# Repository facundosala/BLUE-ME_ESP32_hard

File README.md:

# BLUE-ME_ESP32_hardware
Hardware esp32 for use Blue And Me

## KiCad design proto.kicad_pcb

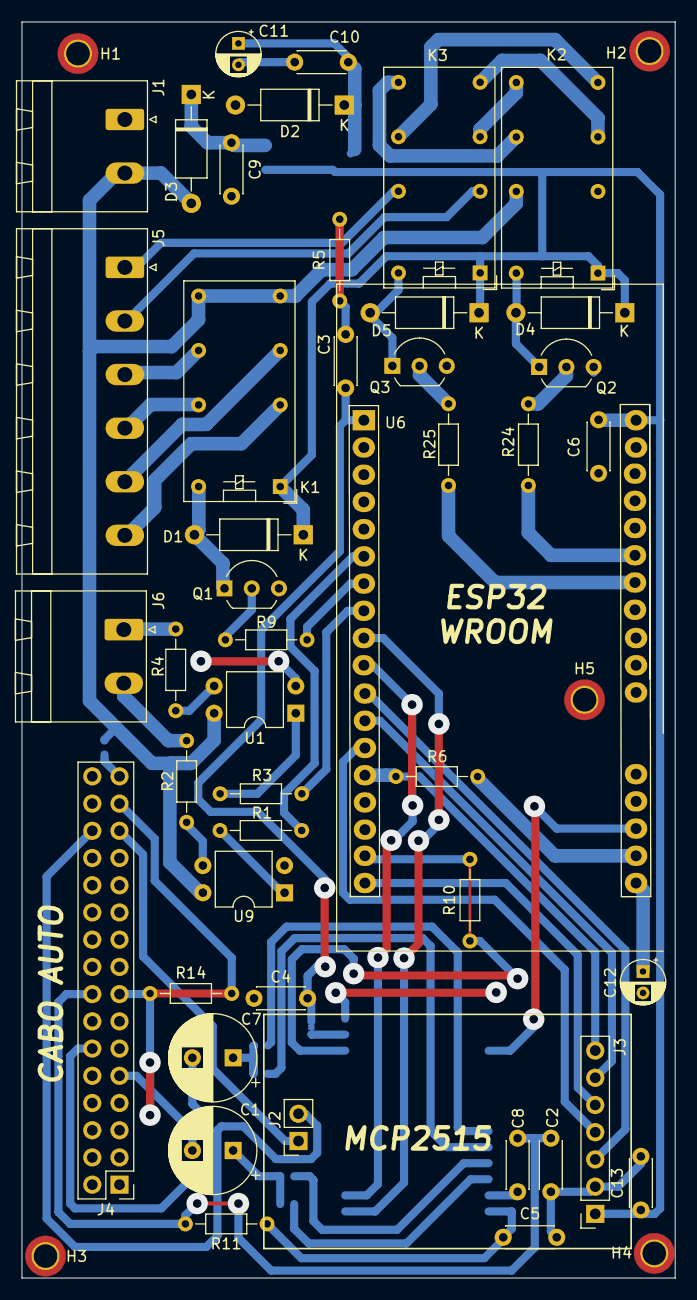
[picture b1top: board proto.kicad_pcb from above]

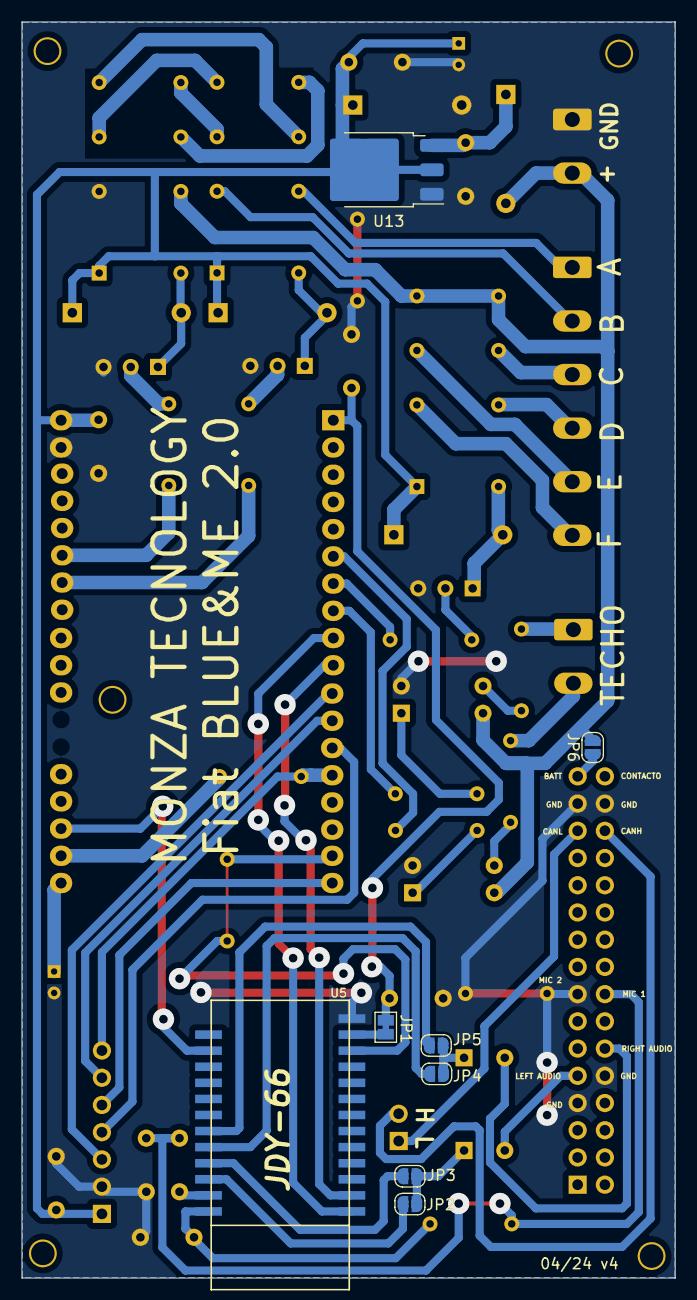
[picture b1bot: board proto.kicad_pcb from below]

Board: 2 copper layers, 61.0 x 117.2 mm, 58 parts (8 on the bottom side), 58 nets.

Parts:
C1, C7: 220uf; CP_Radial_D8.0mm_P3.80mm
C2: 100nf; C_Disc_D4.3mm_W1.9mm_P5.00mm
C3, C4, C6, C9, C10, C13: 100n; C_Disc_D4.3mm_W1.9mm_P5.00mm
C5, C8: 1uf; C_Disc_D4.3mm_W1.9mm_P5.00mm
C11: 10u; CP_Radial_D4.0mm_P2.00mm
C12: 1uf; CP_Radial_D4.0mm_P2.00mm
D1, D4, D5: 1N4007; D_A-405_P10.16mm_Horizontal
D2: P6KE12A; D_A-405_P10.16mm_Horizontal
D3: D_Schottky 1N5819; D_A-405_P10.16mm_Horizontal
H1, H2, H3, H4, H5: MountingHole_Pad; MountingHole_2.2mm_M2_DIN965_Pad_TopOnly
J1: Bateria; PhoenixContact_MSTBA_2,5_2-G_1x02_P5.00mm_Horizontal
J2: CAN_MCP; PinSocket_1x02_P2.54mm_Vertical
J3: MCP2515; PinSocket_1x07_P2.54mm_Vertical
J4: CABO_AUTO; PinHeader_2x16_P2.54mm_Vertical
J5: Señales; PhoenixContact_MSTBA_2,5_6-G_1x06_P5.00mm_Horizontal
J6: Alimentacion; PhoenixContact_MSTBA_2,5_2-G_1x02_P5.00mm_Horizontal
JP1: 5V; SolderJumper-2_P1.3mm_Bridged_Pad1.0x1.5mm
JP2, JP3, JP4, JP5, JP6: SolderJumper_2_Open; SolderJumper-2_P1.3mm_Open_RoundedPad1.0x1.5mm
K1, K2, K3: EC2-3NU; Relay_DPDT_Omron_G5V-2
Q1, Q2, Q3: BC547; TO-92_Inline_Wide
R1, R3: 150; R_Axial_DIN0204_L3.6mm_D1.6mm_P7.62mm_Horizontal
R2, R4: 120; R_Axial_DIN0204_L3.6mm_D1.6mm_P7.62mm_Horizontal
R5, R10, R14: 0; R_Axial_DIN0204_L3.6mm_D1.6mm_P7.62mm_Horizontal
R6: 1K; R_Axial_DIN0204_L3.6mm_D1.6mm_P7.62mm_Horizontal
R9, R11, R24, R25: 1k; R_Axial_DIN0204_L3.6mm_D1.6mm_P7.62mm_Horizontal
U1, U9: EL817; DIP-4_W7.62mm
U5: JDY-66; JDY-18
U6: ESP32-DEVKIT-V1; ESP32_DEVKIT11
U13: LM1117DT-5.0; TO-252-3_TabPin2

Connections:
+3.3VP: C3.1, C4.1, JP1.2 (B), U6.1 (3V3)
+5V: C6.1, C10.1, C11.1, C13.1, D1.1 (K), D2.1 (K), D4.1 (K), D5.1 (K), J3.1, K1.1, K2.1, K3.1, U6.19 (VIN), U13.2 (VO)
+12V: C9.1, D3.1 (K), U13.3 (VI)
BATT+: D3.2 (A), J1.2, JP6.2 (B), K1.8, K1.9, K2.13, U1.4, U9.4
BATT-: C2.2, C3.2, C4.2, C5.2, C6.2, C9.2, C10.2, C11.2, C12.2, C13.2, D2.2 (A), J1.1, J3.2, J4.7, J4.10, J4.15, J4.29, J4.30, K2.4, Q1.3 (E), Q2.3 (E), Q3.3 (E), R5.1, R5.2, R14.1, R14.2, U1.2, U5.13 (GND), U6.20 (GND), U9.2, U13.1 (GND)
CANH_50: J2.2, J4.28
CANL_50: J2.1, J4.27
CLOSE_MIRR: R25.1, U6.25 (D12)
CLOSE_MIRR_CAR: J5.1, K3.13
CLOSE_TECH: R3.1, U6.8 (D4)
CLOSE_TECH_CAR: J6.1, R4.2
CS: J3.3, U6.11 (D5)
ESTADOBT: U5.15 (ASTAT), U6.34 (VN)
INT: J3.7, R6.1, U6.14 (D21)
L: C1.2, J4.9
MIC 1: C2.1, C8.1, J4.16, R11.1
MIRROR+: J5.6, K1.4
MIRROR+': J5.5, K1.6
unnamed: D1.2 (A), K1.16, Q1.1 (C)
unnamed: D4.2 (A), K2.16, Q2.1 (C)
unnamed: D5.2 (A), K3.16, Q3.1 (C)
unnamed: J4.31, JP6.1 (A)
unnamed: JP1.1 (A), U5.12 (VCC)
unnamed: JP2.1 (A), U5.23 (LP)
unnamed: C1.1, JP2.2 (B), JP3.2 (B)
unnamed: JP3.1 (A), U5.22 (LN)
unnamed: JP4.1 (A), U5.21 (RN)
unnamed: C7.1, JP4.2 (B), JP5.2 (B)
unnamed: JP5.1 (A), U5.20 (RP)
unnamed: K2.6, K3.8
unnamed: K2.8, K3.11
unnamed: K2.9, K3.6
unnamed: K2.11, K3.9
unnamed: Q1.2 (B), R9.2
unnamed: Q2.2 (B), R24.2
unnamed: Q3.2 (B), R25.2
unnamed: R1.2, U9.1
unnamed: R2.1, U9.3
unnamed: R3.2, U1.1
unnamed: R4.1, U1.3
unnamed: C8.2, U5.24 (MIC-IN)
unnamed: C5.1, R11.2, U5.25 (MIC-VCC)
unnamed: C12.1, U6.36 (EN)
OPEN_MIRR: R24.1, U6.24 (D13)
OPEN_MIRR_CAR: J5.2, K3.4
OPEN_TECH: R1.1, U6.6 (D15)
OPEN_TECH_CAR: J6.2, R2.2
POWER: R9.1, U6.7 (D2)
R: C7.2, J4.12
RTSAUDIO: R10.1, R10.2, U5.11 (RESET), U6.17 (D22)
RXAUDIO: U5.2 (RXD), U6.10 (TX2)
SCK: J3.6, U6.12 (D18)
SI: J3.5, U6.18 (D23)
SLEEP: R6.2, U6.35 (VP)
SO: J3.4, U6.13 (D19)
TECHO+: J5.4, K1.13
TECHO+': J5.3, K1.11
TXAUDIO: U5.1 (TXD), U6.9 (RX2)
